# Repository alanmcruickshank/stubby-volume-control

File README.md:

# stubby-volume-control
A distinctly over engineered USB volume control designed in OpenSCAD and programmed using Arduino

## Contents
- [Design](/scad/design.md)
- [Programming](/cpp/programming.md)
- [Assembly](/docs/assembly.md)

## TODO

- Add all the scad files and some explanation of what they do (a branch for the original version first and then a dev branch for the new version)
- Add a full set of stl files and the tag that as a *release* before changing them all.
- Add some docs around print settings for best results, especially for the geared components. i.e. RAFTS!

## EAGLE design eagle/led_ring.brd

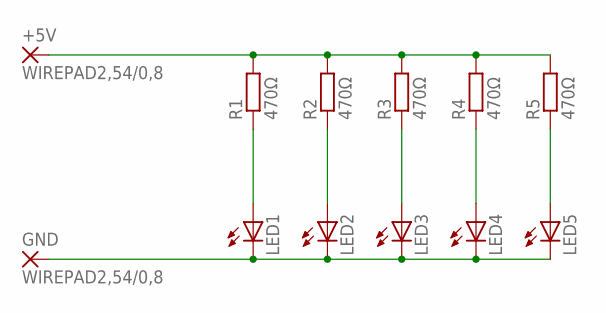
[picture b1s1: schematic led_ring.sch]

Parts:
+5V: WIREPAD2,54/0,8; 2,54/0,8
GND: WIREPAD2,54/0,8; 2,54/0,8
LED1, LED2, LED3, LED4, LED5: LED5MM
R1, R2, R3, R4, R5: 470Ω; 0204/7

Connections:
unnamed: LED1.A, R1.1
unnamed: LED2.A, R2.1
unnamed: LED3.A, R3.1
unnamed: LED4.A, R4.1
unnamed: LED5.A, R5.1
unnamed: +5V.1, R1.2, R2.2, R3.2, R4.2, R5.2
unnamed: GND.1, LED1.K (C), LED2.K (C), LED3.K (C), LED4.K (C), LED5.K (C)

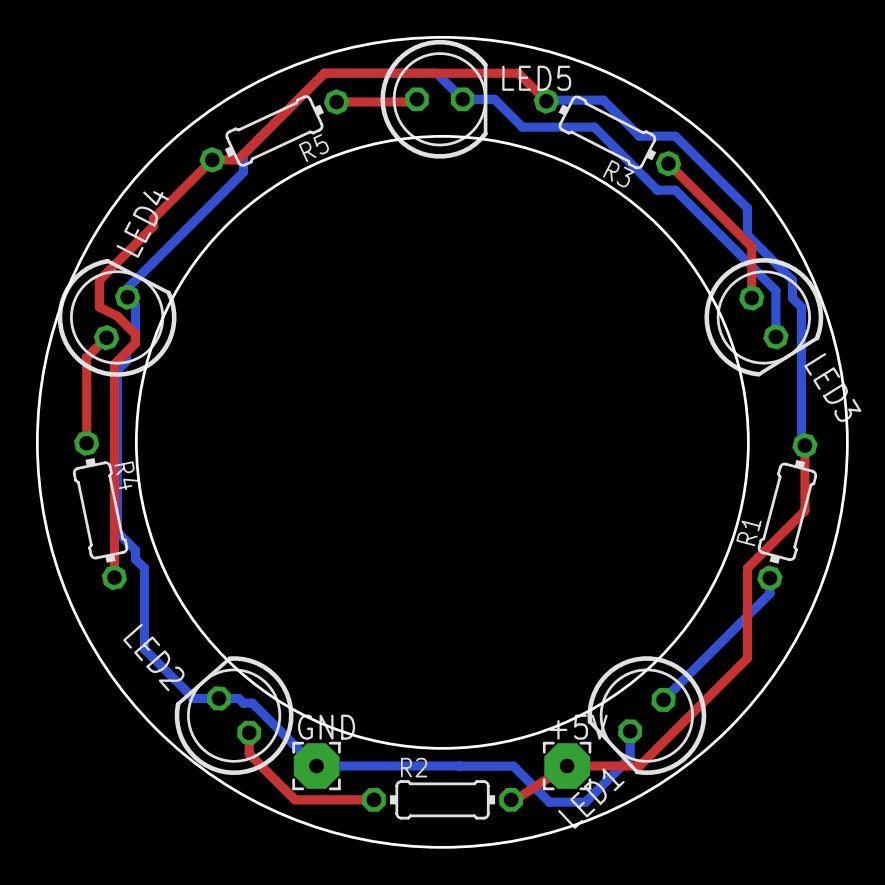
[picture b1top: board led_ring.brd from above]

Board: 2 copper layers, 45.0 x 45.0 mm, 12 parts (0 on the bottom side), 7 nets.

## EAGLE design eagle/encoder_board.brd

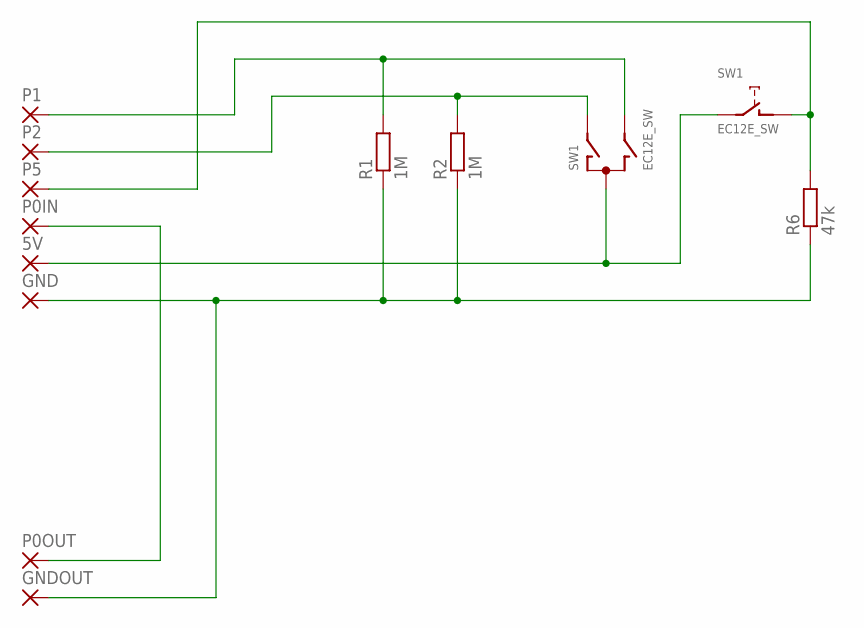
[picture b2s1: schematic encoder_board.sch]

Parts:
5V: 2,54/0,8
GND: 2,54/0,8
GNDOUT: 2,54/0,8
P0IN, P0OUT, P1, P2, P5: 2,54/0,8
R1, R2: 1M; 0204/7
R6: 47k; 0204/7
SW1: EC12E_SW; ALPS_EC12E_SW

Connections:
GND2: GND.1, GNDOUT.1, R1.1, R2.1, R6.1
unnamed: P0IN.1, P0OUT.1
unnamed: P5.1, R6.2, SW1.D (1)
unnamed: P2.1, R2.2, SW1.A
unnamed: P1.1, R1.2, SW1.B
unnamed: 5V.1, SW1.C, SW1.E (2)

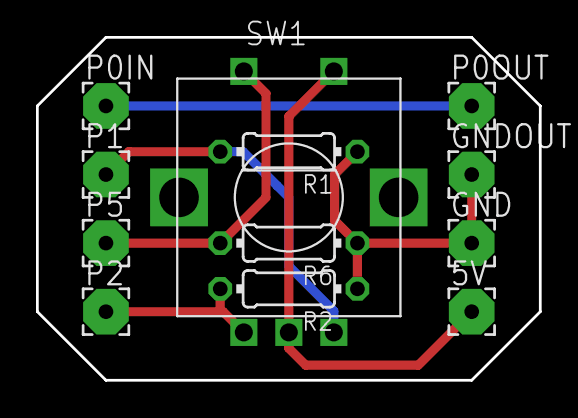
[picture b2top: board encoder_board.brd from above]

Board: 2 copper layers, 27.9 x 19.1 mm, 12 parts (0 on the bottom side), 6 nets.

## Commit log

2018-03-02 Basic docs and a todo - adding a framework before transititioning things over into the git repo
2018-03-02 A version of the arduino sketch with *does* compile, but the multimedia keys aren't working. Need work on porting some more of the trinket library across.
2018-03-02 Adding and cleaning the first stages of the alpha model
2018-03-02 Add Eagle files
2018-03-03 Arduino code works again!
2018-03-05 Finish the upper gearbox assembly in scad and add in some pictures.
2018-03-05 change references to absolute ones
2018-03-06 add the rest of the lower assembly (ex boards at the moment)
2018-06-01 Upgrade firmware to allow skip forward and backward while button is pressed. Only play or pause on button up (rather than down) and only if no tracks skipped.
2018-06-18 a little bit of disconnect logic as a trial to see whether it fixes the disconnect issue
2018-06-19 Big refactor to make the code a little more edible. Be more efficient with datatypes too.
2018-06-19 Refactor of firmware to fix the issue of not connecting until a button pressed. Also added the bump brightness feature so that brightness is a bit smoother.
2018-06-27 Indentation linting
2018-06-27 Add a little delay post reconnect to allow things to reassert
